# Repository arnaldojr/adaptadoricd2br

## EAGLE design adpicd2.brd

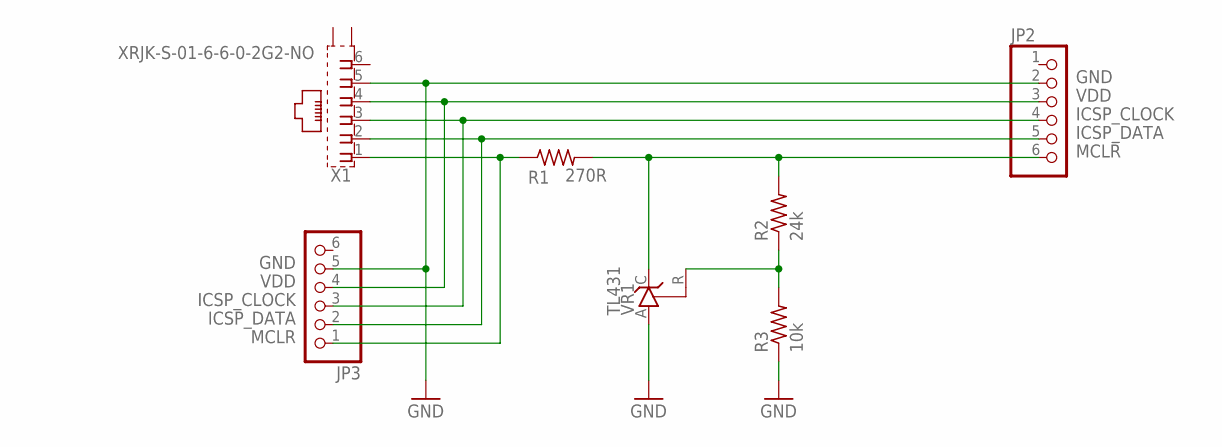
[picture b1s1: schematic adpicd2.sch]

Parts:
JP2, JP3: PINHD-1X6; 1X06
R1: 270R; 0204/5
R2: 24k; 0204/5
R3: 10k; 0204/5
VR1: TL431; TO92-CLP
X1: XRJK-S-01-6-6-0-2G2-NO

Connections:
GND: JP2.2, JP3.5, R3.1, VR1.A, X1.5
unnamed: R2.1, R3.2, VR1.R
unnamed: JP2.6, R1.2, R2.2, VR1.C
unnamed: JP3.1, R1.1, X1.1
unnamed: JP2.3, JP3.4, X1.4
unnamed: JP2.5, JP3.2, X1.2
unnamed: JP2.4, JP3.3, X1.3

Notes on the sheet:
MCLR
VDD
ICSP_DATA
ICSP_CLOCK
GND

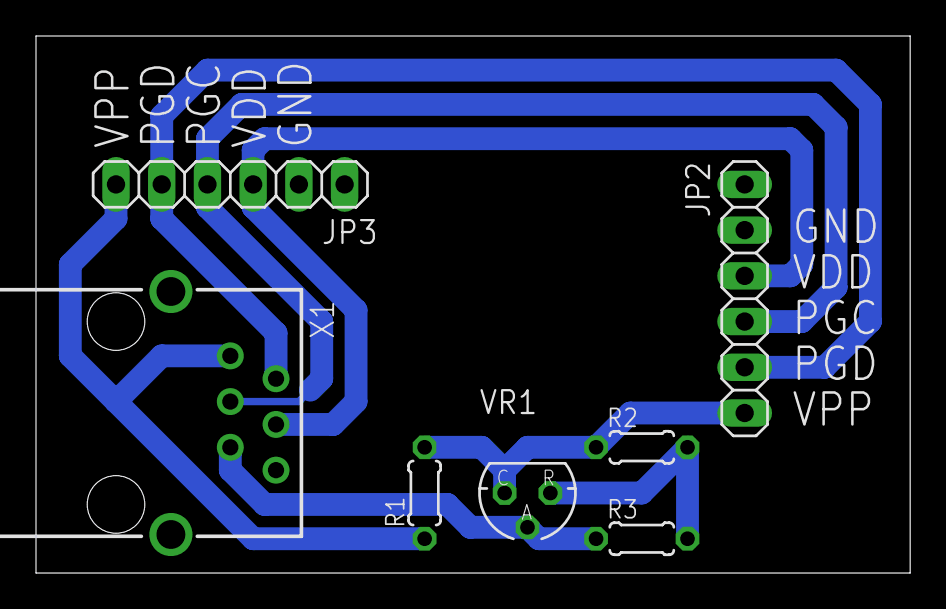
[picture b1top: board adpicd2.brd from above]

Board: 2 copper layers, 48.6 x 29.8 mm, 7 parts (0 on the bottom side), 7 nets.

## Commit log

2018-11-02 init commit
